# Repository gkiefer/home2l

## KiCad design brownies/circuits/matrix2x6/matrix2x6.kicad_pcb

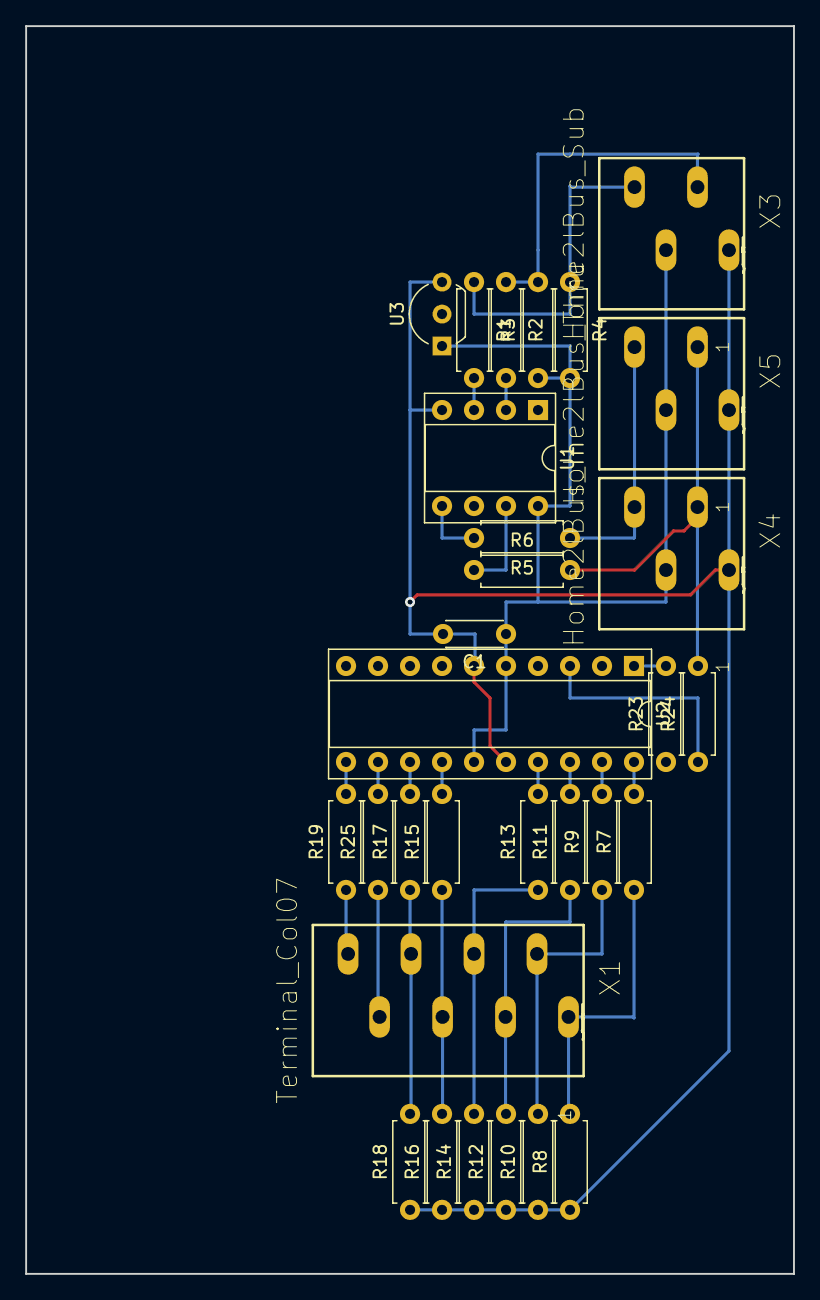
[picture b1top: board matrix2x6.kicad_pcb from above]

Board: 4 copper layers, 61.0 x 99.1 mm, 30 parts (0 on the bottom side), 29 nets.

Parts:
C1: 100nF; C_Disc_D4.3mm_W1.9mm_P5.00mm
R1, R2, R5, R6, R19, R23, R24, R25: 100; R_Axial_DIN0207_L6.3mm_D2.5mm_P7.62mm_Horizontal
R3, R4, R7, R9, R11, R13, R15, R17: 1k; R_Axial_DIN0207_L6.3mm_D2.5mm_P7.62mm_Horizontal
R8, R10, R12, R14, R16, R18: 10k; R_Axial_DIN0207_L6.3mm_D2.5mm_P7.62mm_Horizontal
U1: ATtiny85V-10PU; DIP-8_W7.62mm_Socket
U2: ATtiny861-20PU; DIP-20_W7.62mm_Socket
U3: TSIC306-TO92; TO-92_Inline_Wide
X1: Terminal_Col07; P-250-408
X3: Home2lBus_Sub; P-250-404
X4: Home2lBus_In; P-250-404
X5: Home2lBus_Thru; P-250-404

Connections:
+5V: C1.1, R3.1, R4.2, U1.8, U2.5, U2.15, U3.1, X3.L3, X4.L3, X5.L3
/SCL: R6.2, R24.2, X4.L2, X5.L2
/SDA: R5.1, R23.1, X4.L4, X5.L4
/twi_ma_scl: R2.2, U1.2
/twi_ma_sda: R1.2, U1.3
GND: C1.2, R8.1, R10.1, R12.1, R14.1, R16.1, R18.1, U1.4, U2.6, U2.16, U3.3, X3.L1, X4.L1, X5.L1
unnamed: R1.1, R4.1, X3.L4
unnamed: R2.1, R3.2, X3.L2
unnamed: R5.2, U1.5
unnamed: R6.1, U1.7
unnamed: R7.1, R8.2, X1.L1
unnamed: R7.2, U2.20
unnamed: R9.2, U2.19
unnamed: R9.1, R10.2, X1.L2
unnamed: R11.1, R12.2, X1.L3
unnamed: R11.2, U2.18
unnamed: R13.1, R14.2, X1.L4
unnamed: R13.2, U2.17
unnamed: R15.1, R16.2, X1.L5
unnamed: R15.2, U2.14
unnamed: R17.1, R18.2, X1.L6
unnamed: R17.2, U2.13
unnamed: R19.1, X1.L8
unnamed: R19.2, U2.11
unnamed: R23.2, U2.1
unnamed: R24.1, U2.3
unnamed: R25.1, X1.L7
unnamed: R25.2, U2.12
unnamed: U2.2, U3.2

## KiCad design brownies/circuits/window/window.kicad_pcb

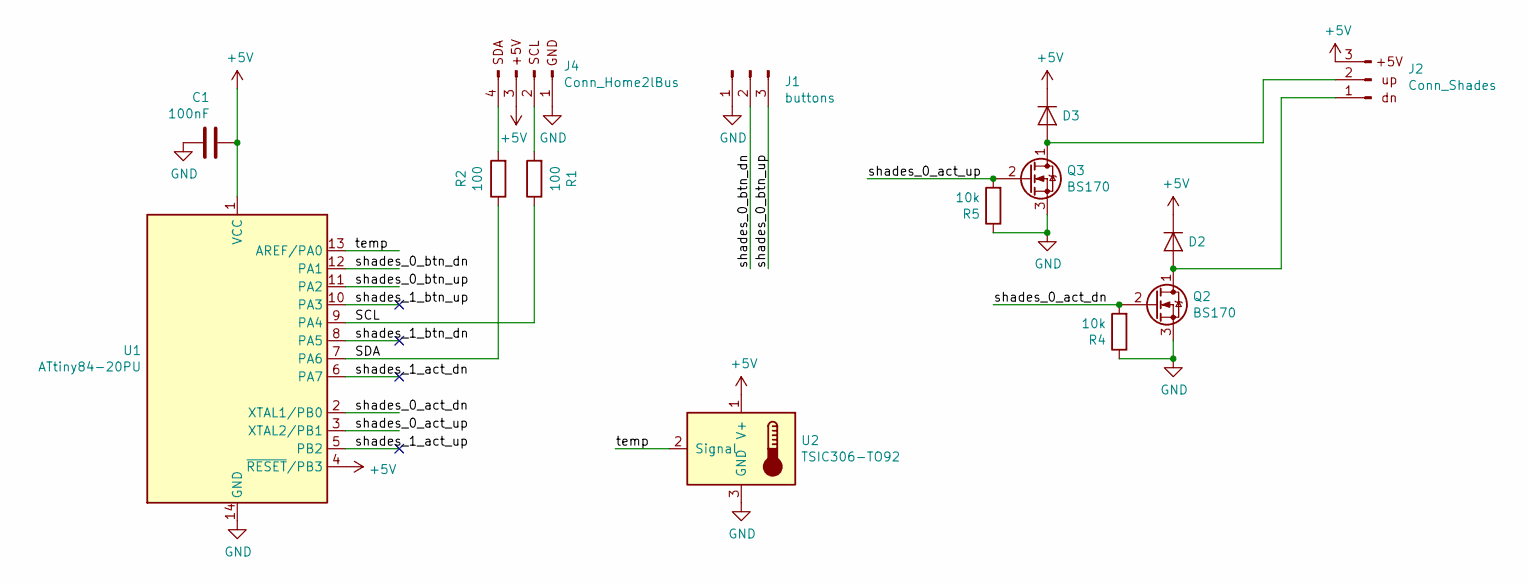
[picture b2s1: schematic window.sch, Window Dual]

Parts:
C1: 100nF; C_Disc_D4.3mm_W1.9mm_P5.00mm
D2, D3: D; D_T-1_P5.08mm_Horizontal
J1: buttons; PinHeader_1x03_P2.54mm_Vertical
J2: Conn_Shades
J4: Conn_Home2lBus
Q2, Q3: BS170; TO-92_Inline_Wide
R1, R2: 100; R_Axial_DIN0204_L3.6mm_D1.6mm_P7.62mm_Horizontal
R4, R5: 10k; R_Axial_DIN0204_L3.6mm_D1.6mm_P7.62mm_Horizontal
U1: ATtiny84-20PU; DIP-14_W7.62mm_Socket
U2: TSIC306-TO92; TO-92_Inline_Wide

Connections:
+5V: C1.1, D2.1 (K), D3.1 (K), J2.3, J4.3, U1.1 (VCC), U1.4 (~RESET~/PB3), U2.1 (V+)
/SCL: R1.1, U1.9 (PA4)
/SDA: R2.1, U1.7 (PA6)
/shades_0_act_dn: Q2.2 (G), R4.2, U1.2 (XTAL1/PB0)
/shades_0_act_up: Q3.2 (G), R5.2, U1.3 (XTAL2/PB1)
/shades_0_btn_dn: J1.2, U1.12 (PA1)
/shades_0_btn_up: J1.3, U1.11 (PA2)
/shades_1_act_dn: U1.6 (PA7)
/shades_1_act_up: U1.5 (PB2)
/shades_1_btn_dn: U1.8 (PA5)
/shades_1_btn_up: U1.10 (PA3)
/temp: U1.13 (AREF/PA0), U2.2 (Signal)
GND: C1.2, J1.1, J4.1, Q2.3 (S), Q3.3 (S), R4.1, R5.1, U1.14 (GND), U2.3 (GND)
unnamed: D2.2 (A), J2.1, Q2.1 (D)
unnamed: D3.2 (A), J2.2, Q3.1 (D)
unnamed: J4.2, R1.2
unnamed: J4.4, R2.2

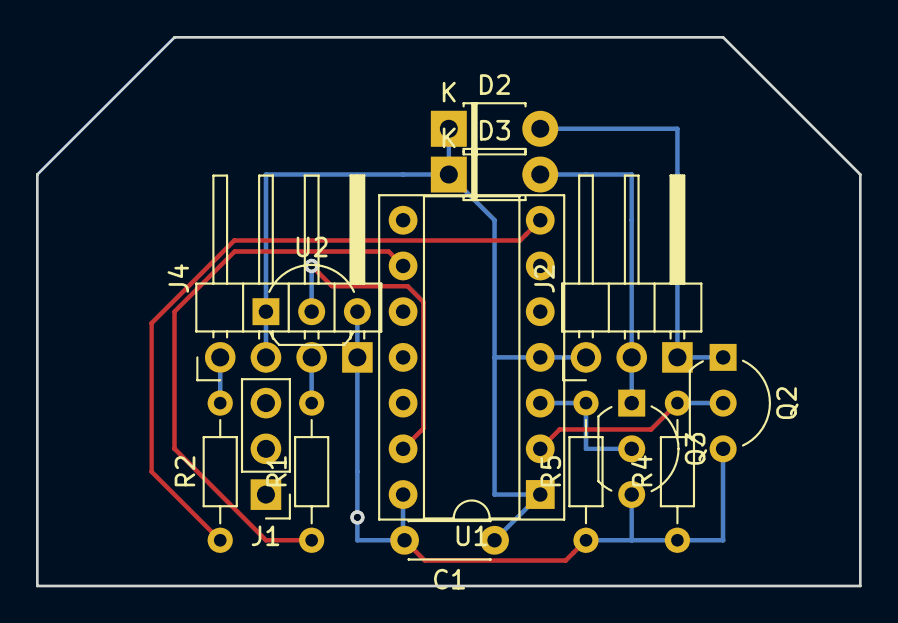
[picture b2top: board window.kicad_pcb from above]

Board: 4 copper layers, 45.7 x 30.5 mm, 14 parts (0 on the bottom side), 13 nets.
